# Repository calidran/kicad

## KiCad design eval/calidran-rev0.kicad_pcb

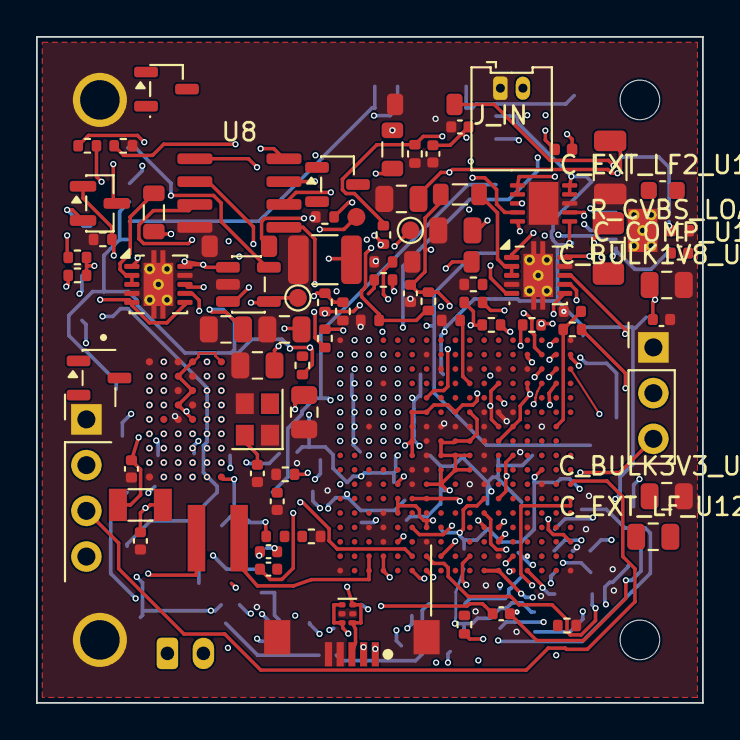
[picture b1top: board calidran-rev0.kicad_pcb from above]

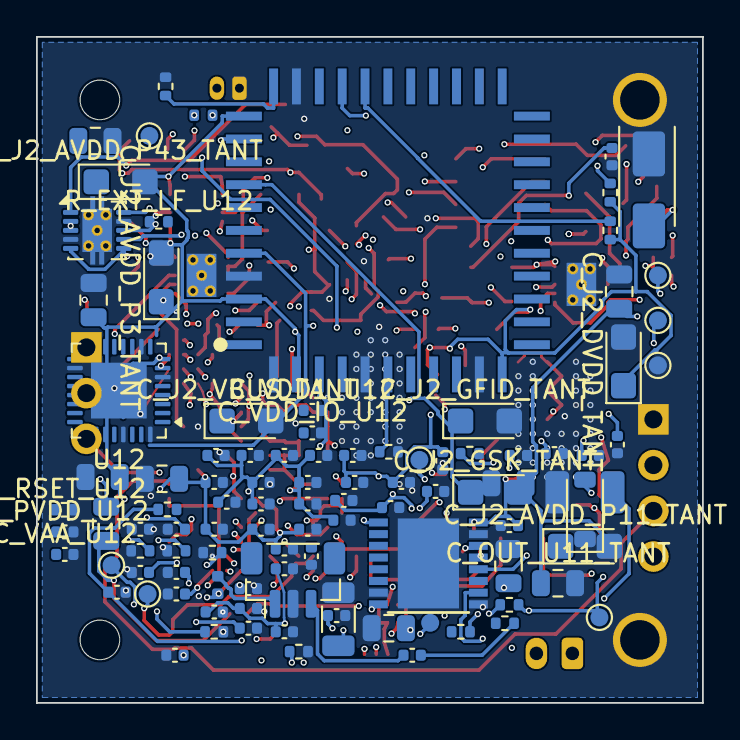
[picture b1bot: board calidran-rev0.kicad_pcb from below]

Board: 10 copper layers, 37.0 x 37.0 mm, 189 parts (101 on the bottom side), 140 nets.

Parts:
C1: 10uF_10V_X7R_0805; C_0805_2012Metric
C2, C5: 10uF_6V3_X5R_0805; C_0805_2012Metric
C3, C6: 4.7uF_6V3_X5R_0402; C_0402_1005Metric
C4: 10uF_25V_X5R; C_0805_2012Metric
C7: 10uF_25V_X7R_1206; C_1206_3216Metric
C8: 47uF_10V_X5R_1210; C_1210_3225Metric
C9, C14: 10uF_10V_X5R_0805; C_0805_2012Metric
C10, C11, C13: 100nF; C_0402_1005Metric
CFLY: 100nF_X5R_0402; C_0402_1005Metric
CVCP: 100nF; C_0402_1005Metric
CX1, CX2: 18pF_C0G_0402; C_0402_1005Metric
CX3, CX4: 6pF_C0G_0402_DNP; C_0402_1005Metric
C_ADC_VREF: 100nF; C_0402_1005Metric
C_ADJ_U11: 10nF_C0G; C_0402_1005Metric
C_ANA1: 2.2uF_0402; C_0402_1005Metric
C_BULK1V8_U12, C_BULK3V3_U12: 10uF_10V_X7R_0805; C_0805_2012Metric
C_COMP_U12: 2.2nF; C_0402_1005Metric
C_CVBS_AC: 100nF; C_0402_1005Metric
C_EXT_LF2_U12: 150nF; C_0603_1608Metric
C_EXT_LF_U12: 12nF; C_0805_2012Metric
C_FID_RSVR: 10uF; C_0402_1005Metric
C_IN_U11_FILM: 100nF; C_0805_2012Metric
C_IN_U11_TANT: 10uF_Tant; CP_EIA-3528-21_Kemet-B
C_J2_AVDD_P3_FILM, C_J2_AVDD_P11_FILM, C_J2_AVDD_P43_FILM, C_J2_DVDD_FILM, C_J2_GFID_FILM, C_J2_GSK_FILM, C_J2_VBUS_FILM: 100nF; C_0805_2012Metric
C_J2_AVDD_P3_TANT, C_J2_AVDD_P11_TANT, C_J2_AVDD_P43_TANT, C_J2_DVDD_TANT, C_J2_GFID_TANT, C_J2_GSK_TANT, C_J2_VBUS_TANT: 22uF_Tant; CP_EIA-3216-18_Kemet-A
C_J2_VRIN_FILM: 4.7uF; C_1206_3216Metric
C_LPSR_A: 100nF_0402; C_0402_1005Metric
C_LPSR_D: 100nF_0402; C_0402_1005Metric
C_MIPI1P0: 1uF_0402; C_0402_1005Metric
C_OUT_U11_FILM: 100nF; C_0805_2012Metric
C_OUT_U11_TANT: 10uF_16V_X7R; C_0805_2012Metric
C_PSWITCH: 100nF; C_0402_1005Metric
C_PVDD_U12: 100nF; C_0402_1005Metric
C_SNVS_A: 100nF_0402; C_0402_1005Metric
C_SNVS_D: 100nF_0402; C_0402_1005Metric
C_U6_1, C_U6_2, C_U6_3, C_U6_4, C_U6_5, C_U6_6, C_U6_15, C_U6_16, C_U6_17, C_U6_18, C_U6_19, C_U6_20, C_U6_21, C_U6_22, C_U6_23, C_U6_24, C_U6_25, C_U6_26, C_U7_1, C_U7_2, C_U7_3, C_U7_4: 100nF_X5R_0402; C_0402_1005Metric
C_U6_7, C_U6_8, C_U6_9, C_U6_10, C_U6_27, C_U6_28: 10uF_6V3_X5R_0402; C_0402_1005Metric
C_U6_11, C_U6_12, C_U6_13, C_U6_14: 10nF_X5R_0402; C_0402_1005Metric
C_VAA_U12: 100nF; C_0402_1005Metric
C_VDD1_U12: 100nF; C_0402_1005Metric
C_VDDA1P0: 2.2uF_0402; C_0402_1005Metric
C_VDD_IO_U12: 100nF; C_0402_1005Metric
C_VSYS_MON: 100nF; C_0402_1005Metric
D1: SMAJ18CA; D_SMA
D_FID: BAT54T3G; SOT-23-3
F1: MF-MSMF110/16X; Fuse_1206_3216Metric
FB1: FerriteBead_600R@100MHz; L_0402_1005Metric
F_VID: FSMD010-0402RZ; Fuse_0402_1005Metric
J2: PLU-044-H901-99; Conn_01x44_J_LEAD
JP1_BOOT: BOOT_MODE_JUMPER_DNP; PinHeader_1x03_P2.54mm_Vertical
J_3V3_SHUNT: 0R_DNP; R_0402_1005Metric
J_IN: Molex_PicoBlade_53048-0210_1x02_P1.25mm_Horizontal
J_SHUTTER: JST_PH_B2B-PH-K_1x02_P2.00mm_Vertical
J_UART: UART_Header_2.54mm; PinHeader_1x04_P2.54mm_Vertical
J_USB: USB_Micro-AB_Hirose_ZX62-AB-5PA
J_VIDEO: JST-SH_3pin_Video; JST_SH_BM03B-SRSS-TB_1x03-1MP_P1.00mm_Vertical
L1, L2, L3: 1uH_3A_Wurth_744066100; L_0805_2012Metric
L_DCDC: 4.7uH WE-MAPI; L_Wuerth_MAPI-4030
MK1, MK3: MountingHole_2.2mm_M2_Pad_R30
MK2, MK4: MountingHole_2.2mm_M2
Q1: SI2319DS-T1-GE3; SOT-23
Q_FID_N: 2N7002; SOT-23-3
Q_FID_P: Si2301CDS; SOT-23-3
R1: 49.9k; R_0402_1005Metric
R2: 200k; R_0402_1005Metric
R3: 124k; R_0402_1005Metric
R4, R6: 100k; R_0402_1005Metric
R5: 316k; R_0402_1005Metric
R_ADC_VREF: 10R; R_0402_1005Metric
R_BOOT_MODE0: 100k; R_0402_1005Metric
R_BOOT_MODE1: 4.7k; R_0402_1005Metric
R_BT_CFG0, R_BT_CFG1, R_BT_CFG4: 100k; R_0402_1005Metric
R_CVBS_LOAD: 75; R_0402_1005Metric
R_CVBS_SER: 75; R_0402_1005Metric
R_ENC_RESET_PU: 10k; R_0402_1005Metric
R_EN_U11: 100k; R_0402_1005Metric
R_EXT_LF_U12: 169; R_0402_1005Metric
R_FID: 10k; R_0402_1005Metric
R_G1: 1M; R_0402_1005Metric
R_HOLD: 10k; R_0402_1005Metric
R_ILIM_U11: DNP; R_0402_1005Metric
R_IPROPI: 10k; R_0402_1005Metric
R_J2_I2CAD, R_J2_SEQ_TRIG: 10k; R_0402_1005Metric
R_J2_SCL, R_J2_SDA: 4.7k; R_0402_1005Metric
R_JTAG_MOD: 4k7; R_0402_1005Metric
R_JTAG_TRST: 4k7; R_0402_1005Metric
R_NFAULT: 100k; R_0402_1005Metric
R_NSLEEP: 100k; R_0402_1005Metric
R_ONOFF: 100k; R_0402_1005Metric
R_PG1V0, R_PG1V8, R_PG3V3: 100k; R_0402_1005Metric
R_PG_U11: 100k; R_0402_1005Metric
R_PSWITCH: 100k; R_0402_1005Metric
R_RSET_U12: 510; R_0402_1005Metric
R_SET_U11: 37.4k; R_0402_1005Metric
R_TEST_MODE: 4k7; R_0402_1005Metric
R_VSYS_H: 100k; R_0402_1005Metric
R_VSYS_L: 22k1; R_0402_1005Metric
R_WAKEUP: 100k; R_0402_1005Metric
R_WP: 10k; R_0402_1005Metric
R_nRESET: 100k; R_0402_1005Metric
TP_3V3: TestPoint_Pad_D1.0mm
TP_BM0: TP_BM0; TestPoint_Pad_D1.0mm
TP_BM1: TP_BM1; TestPoint_Pad_D1.0mm
TP_GND: TestPoint_Pad_D1.0mm
TP_PG1V0: TP_PG1V0; TestPoint_Pad_D1.0mm
TP_PG1V8: TP_PG1V8; TestPoint_Pad_D1.0mm
TP_PG3V3: TP_PG3V3; TestPoint_Pad_D1.0mm
TP_PGOOD: TP_PGOOD; TestPoint_Pad_D1.0mm
TP_SWDCLK: TestPoint_Pad_D1.0mm
TP_SWDIO: TestPoint_Pad_D1.0mm
TP_SWO: TestPoint_Pad_D1.0mm
TP_nRST: TestPoint_Pad_D1.0mm
U1, U2, U3: TPS62130ARGTR; VSON-10-1EP_3x3mm_P0.5mm_EP1.65x2.4mm_ThermalVias
U4: TPS3840DL30DCKR; SOT-23-5
U6: MIMXRT1176DVMAA; MAPBGA-289_14x14mm_Layout17x17_P0.8mm
U7: AS4C32M16SB-7BIN
U8: W25Q128JV-IQ; SOIC-8_3.9x4.9mm_P1.27mm
U9: TPD4S012DRYR; Texas_USON-6_1x1.45mm_P0.5mm_SMD
U10: DRV8876PWPR; HTSSOP-16-1EP
U11: LT3045EDD#PBF; DFN-10-1EP_3x3mm_P0.5mm_EP1.65x2.38mm
U12: ADV7391BCPZ; QFN-32-1EP_5x5mm_P0.5mm_EP3.1x3.1mm
X1: 24MHz_NDK_NX2520SA-24.000MHZ; Crystal_SMD_2520-4Pin_2.5x2.0mm
X2: 32.768kHz_Epson_FC-135R_DNP; Crystal_SMD_3215-2Pin_3.2x1.5mm
Z1, Z2, Z3: BZT52C5V6-7-F; D_SOD-123
Z_G1: BZT52C5V6-7-F; D_SOD-123

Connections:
+1V8: C5.2, C6.2, C_BULK1V8_U12.1, C_EXT_LF2_U12.2, C_EXT_LF_U12.2, C_J2_DVDD_FILM.1, C_J2_DVDD_TANT.1, C_PVDD_U12.1, C_U6_5.2, C_U6_6.2, C_U6_23.2, C_U6_24.2, C_U6_25.2, C_U6_26.2, C_U6_27.2, C_U6_28.2, C_VDD1_U12.1, J2.34, L2.1, R3.1, R_J2_SCL.1, R_J2_SDA.1, R_PG1V8.1, U2.10, U6.D14, U6.F6, U6.F7, U6.F9, U6.G6, U6.G13, U6.H6, U6.H12, U6.J6, U6.K15, U6.M11, U12.5, U12.17, U12.28
+3V3: C8.2, C9.2, C11.2, C13.2, C14.2, C_BULK3V3_U12.1, C_COMP_U12.2, C_FID_RSVR.1, C_U7_1.2, C_U7_2.2, C_U7_3.2, C_U7_4.2, C_VAA_U12.1, C_VDD_IO_U12.1, FB1.2, F_VID.1, J_3V3_SHUNT.2, J_UART.2, L3.1, R5.1, R_BOOT_MODE1.1, R_ENC_RESET_PU.1, R_EN_U11.1, R_HOLD.2, R_JTAG_TRST.2, R_NFAULT.1, R_NSLEEP.1, R_PG3V3.1, R_PSWITCH.2, R_WP.2, TP_3V3.1, U3.10, U4.1, U4.3, U6.D12, U6.E7, U6.G12, U6.J13, U6.M5, U6.M12, U6.N5, U6.P7, U6.R12, U6.U11, U6.U12, U7.A4, U7.A6, U7.B3, U7.C4, U7.D3, U7.E4, U7.J6, U8.8, U10.5, U10.16, U12.1, U12.19
+12V_IN: C1.2, C4.2, C7.2, CVCP.2, D1.2, Q1.2, U1.5, U1.6, U2.5, U2.6, U3.5, U3.6, U10.11
/+1V0: C2.2, C3.2, C_MIPI1P0.2, C_U6_1.2, C_U6_2.2, C_U6_3.2, C_U6_4.2, C_U6_7.2, C_U6_8.2, C_U6_9.2, C_U6_10.2, C_U6_11.2, C_U6_12.2, C_U6_13.2, C_U6_14.2, C_U6_15.2, C_U6_16.2, C_U6_17.2, C_U6_18.2, C_U6_19.2, C_U6_20.2, C_U6_21.2, C_U6_22.2, L1.1, R1.1, R_PG1V0.1, U1.10, U6.F10, U6.H8, U6.H9, U6.H10, U6.J8, U6.J9, U6.J10, U6.K8, U6.K9, U6.K10, U6.L7, U6.L8
/+3V3_MEAS: J_3V3_SHUNT.1, R_ADC_VREF.2, R_ONOFF.2, R_nRESET.2
/+3V3_VID: F_VID.2, J_VIDEO.1
/ADC_VREFH: C_ADC_VREF.2, R_ADC_VREF.1, U6.G16
/BOOT_MODE0: JP1_BOOT.3, R_BOOT_MODE0.2, TP_BM0.1, U6.P6
/BOOT_MODE1: JP1_BOOT.2, R_BOOT_MODE1.2, TP_BM1.1, U6.T7
/CVBS_MID: C_CVBS_AC.1, R_CVBS_SER.2
/DCDC_ANA: C_ANA1.2, U6.M6, U6.M7, U6.M8
/DCDC_IN_Q: FB1.1, U6.L5
/DCDC_LN: L_DCDC.1, U6.T4, U6.U4
/DCDC_LP: L_DCDC.2, U6.T3, U6.U3
/ENC_CLK27: U6.E13, U12.13
/ENC_D0: U6.E10, U12.30
/ENC_D1: U6.C11, U12.31
/ENC_D2: R_BT_CFG0.2, U6.D10, U12.2
/ENC_D3: R_BT_CFG1.2, U6.E12, U12.3
/ENC_D4: U6.A15, U12.4
/ENC_D5: U6.C13, U12.7
/ENC_D6: R_BT_CFG4.2, U6.B14, U12.8
/ENC_D7: U6.A14, U12.9
/EN_1V0: U1.1, Z1.2
/EN_1V8: U2.1, Z2.2
/EN_3V3: U3.1, Z3.2
/EXT_LF_FZ: C_EXT_LF2_U12.1, R_EXT_LF_U12.2
/FB_1V0: R1.2, R2.2, U1.7
/FB_1V8: R3.2, R4.2, U2.7
/FB_3V3: R5.2, R6.2, U3.7
/JTAG_MOD: R_JTAG_MOD.2, U6.U6
/JTAG_TRSTB: R_JTAG_TRST.1, U6.R5
/ONOFF: R_ONOFF.1, U6.U10
/PG_1V0: R_PG1V0.2, TP_PG1V0.1, U1.8
/PG_1V8: R_PG1V8.2, TP_PG1V8.1, U2.8
/PG_3V3: R_PG3V3.2, TP_PG3V3.1, U3.8
/Q1_GATE: Q1.1, R_G1.2, Z_G1.2
/QSPI_CLK: U6.D15, U8.6
/QSPI_CS0_B: U6.B16, U8.1
/QSPI_D0: U6.C15, U8.5
/QSPI_D1: U6.B17, U8.2
/QSPI_D2: R_WP.1, U6.B15, U8.3
/QSPI_D3: R_HOLD.1, U6.A16, U8.7
/RTC_XTAL_IN: CX3.2, U6.T13, X2.1
/RTC_XTAL_OUT: CX4.2, U6.U13, X2.2
/SEMC_A0: U6.A3, U7.G2
/SEMC_A1: U6.A2, U7.G1
/SEMC_A2: U6.C2, U7.J3
/SEMC_A3: U6.C5, U7.H3
/SEMC_A4: U6.D5, U7.J5
/SEMC_A5: U6.B1, U7.H1
/SEMC_A6: U6.C1, U7.J4
/SEMC_A7: U6.D3, U7.J2
/SEMC_A8: U6.B3, U7.H2
/SEMC_A9: U6.B4, U7.H6
/SEMC_A10: U6.B2, U7.G3
/SEMC_A11: U6.C4, U7.H4
/SEMC_A12: U6.C3, U7.H5
/SEMC_BA0: U6.G2, U7.G4
/SEMC_BA1: U6.H2, U7.G5
/SEMC_CAS_B: U6.J4, U7.F4
/SEMC_CKE: U6.E5, U7.F3
/SEMC_CLK: U6.G5, U7.F2
/SEMC_CS0_B: U6.L1, U7.G6
/SEMC_D0: U6.F3, U7.B6
/SEMC_D1: U6.F2, U7.C5
/SEMC_D2: U6.G4, U7.C6
/SEMC_D3: U6.E4, U7.A5
/SEMC_D4: U6.H5, U7.D6
/SEMC_D5: U6.F4, U7.B5
/SEMC_D6: U6.H4, U7.D5
/SEMC_D7: U6.H3, U7.E6
/SEMC_D8: U6.E3, U7.B1
/SEMC_D9: U6.D2, U7.A2
/SEMC_D10: U6.D1, U7.B2
/SEMC_D11: U6.E2, U7.C2
/SEMC_D12: U6.E1, U7.C1
/SEMC_D13: U6.F1, U7.D2
/SEMC_D14: U6.G1, U7.D1
/SEMC_D15: U6.H1, U7.E1
/SEMC_DQM0: U6.F5, U7.E5
/SEMC_DQM1: U6.E6, U7.F1
/SEMC_RAS_B: U6.J5, U7.F5
/SEMC_WE_B: U6.J3, U7.F6
/SHUTTER_IN1: U6.R17, U10.1
/SHUTTER_IN2: U6.P16, U10.2
/SHUTTER_IPROPI: R_IPROPI.1, U6.L12, U10.6
/SHUTTER_NFAULT: R_NFAULT.2, U6.N14, U10.4
/SHUTTER_OUT1: J_SHUTTER.1, U10.8
/SHUTTER_OUT2: J_SHUTTER.2, U10.10
/SH_CPH: CFLY.1, U10.13
/SH_CPL: CFLY.2, U10.14
/SH_NSLEEP: R_NSLEEP.2, U10.3
/SH_VCP: CVCP.1, U10.12
/SWDCLK: TP_SWDCLK.1, U6.T6
/SWDIO: TP_SWDIO.1, U6.U7
/SWO: TP_SWO.1, U6.T5
/SW_1V0: L1.2, U1.2, U1.3
/SW_1V8: L2.2, U2.2, U2.3
/SW_3V3: L3.2, U3.2, U3.3
/SYS_RST_B: R_nRESET.1, TP_PGOOD.1, TP_nRST.1, U4.4, U6.T10
/TEST_MODE: R_TEST_MODE.2, U6.T11
/U4_CT: C10.2, U4.5
/U12_COMP: C_COMP_U12.1, U12.23
/U12_EXT_LF: C_EXT_LF_U12.1, R_EXT_LF_U12.1, U12.16
/U12_RSET: R_RSET_U12.1, U12.24
/UART_RX: J_UART.4, U6.M17
/UART_TX: J_UART.3, U6.L17
/USB_DM: J_USB.2, U6.C16, U9.4, U9.6
/USB_DP: J_USB.3, U6.C17, U9.1, U9.3
/USB_VBUS: J_USB.1, U6.D16
/VDDA_1P0: C_VDDA1P0.2, U6.N11
/VDD_LPSR_ANA: C_LPSR_A.2, U6.P12
/VDD_LPSR_DIG: C_LPSR_D.2, U6.P11
/VDD_SNVS_ANA: C_SNVS_A.2, U6.U14
/VDD_SNVS_DIG: C_SNVS_D.2, U6.T14
/VIN_FUSED: F1.2, Q1.3
/VIN_RAW: F1.1, J_IN.2
/WAKEUP: R_WAKEUP.2, U6.T8
/XTAL24_IN: CX1.2, U6.U16, X1.4
/XTAL24_OUT: CX2.2, U6.T16, X1.2
AVDD: C_ADJ_U11.2, C_J2_AVDD_P3_FILM.1, C_J2_AVDD_P3_TANT.1, C_J2_AVDD_P11_FILM.1, C_J2_AVDD_P11_TANT.1, C_J2_AVDD_P43_FILM.1, C_J2_AVDD_P43_TANT.1, C_J2_GSK_FILM.1, C_J2_GSK_TANT.1, C_OUT_U11_FILM.1, C_OUT_U11_TANT.1, J2.3, J2.11, J2.43, R_PG_U11.2, U11.6, U11.9, U11.10
CVBS_OUT: C_CVBS_AC.2, J_VIDEO.3
CVBS_RAW: R_CVBS_LOAD.1, R_CVBS_SER.1, U12.22
ENC_RESET: R_ENC_RESET_PU.2, U6.R15, U12.14
GND: C1.1, C2.1, C3.1, C4.1, C5.1, C6.1, C7.1, C8.1, C9.1, C10.1, C11.1, C13.1, C14.1, CX1.1, CX2.1, CX3.1, CX4.1, C_ADC_VREF.1, C_ANA1.1, C_BULK1V8_U12.2, C_BULK3V3_U12.2, C_FID_RSVR.2, C_IN_U11_FILM.2, C_IN_U11_TANT.2, C_J2_AVDD_P3_FILM.2, C_J2_AVDD_P3_TANT.2, C_J2_AVDD_P11_FILM.2, C_J2_AVDD_P11_TANT.2, C_J2_AVDD_P43_FILM.2, C_J2_AVDD_P43_TANT.2, C_J2_DVDD_FILM.2, C_J2_DVDD_TANT.2, C_J2_GFID_FILM.2, C_J2_GFID_TANT.2, C_J2_VBUS_FILM.2, C_J2_VBUS_TANT.2, C_J2_VRIN_FILM.2, C_LPSR_A.1, C_LPSR_D.1, C_MIPI1P0.1, C_OUT_U11_FILM.2, C_OUT_U11_TANT.2, C_PSWITCH.1, C_PSWITCH.2, C_PVDD_U12.2, C_SNVS_A.1, C_SNVS_D.1, C_U6_1.1, C_U6_2.1, C_U6_3.1, C_U6_4.1, C_U6_5.1, C_U6_6.1, C_U6_7.1, C_U6_8.1, C_U6_9.1, C_U6_10.1, C_U6_11.1, C_U6_12.1, C_U6_13.1, C_U6_14.1, C_U6_15.1, C_U6_16.1, C_U6_17.1, C_U6_18.1, C_U6_19.1, C_U6_20.1, C_U6_21.1, C_U6_22.1, C_U6_23.1, C_U6_24.1, C_U6_25.1, C_U6_26.1, C_U6_27.1, C_U6_28.1, C_U7_1.1, C_U7_2.1, C_U7_3.1, C_U7_4.1, C_VAA_U12.2, C_VDD1_U12.2, C_VDDA1P0.1, C_VDD_IO_U12.2, C_VSYS_MON.2, D1.1, J2.4, J2.13, J2.35, J2.40, J2.44, JP1_BOOT.1, J_IN.1, J_UART.1, J_USB.4, J_USB.5, J_USB.6, J_VIDEO.2, MK1.1, MK3.1, R2.1, R4.1, R6.1, R_BOOT_MODE0.1, R_BT_CFG0.1, R_BT_CFG1.1, R_BT_CFG4.1, R_CVBS_LOAD.2, R_FID.2, R_G1.1, R_ILIM_U11.2, R_IPROPI.2, R_J2_I2CAD.2, R_J2_SEQ_TRIG.2, R_JTAG_MOD.1, R_PSWITCH.1, R_RSET_U12.2, R_SET_U11.1, R_TEST_MODE.1, R_VSYS_L.2, R_WAKEUP.1, TP_GND.1, U1.4, U1.9, U1.11, U2.4, U2.9, U2.11, U3.4, U3.9, U3.11, U4.2, U6.A1, U6.A17, U6.B7, U6.C8, U6.C10, U6.C12, U6.C14, U6.D4, U6.F11, U6.F12, U6.F13, U6.G3, U6.G7, U6.G8, U6.G9, U6.G10, U6.G11, U6.G15, U6.H7, U6.H11, U6.J7, U6.J11, U6.K6, U6.K7, U6.K11, U6.L3, U6.L6, U6.L10, U6.L11, U6.L15, U6.N4, U6.P3, U6.P4, U6.P14, U6.R4, U6.R7, U6.T12, U6.U1, U6.U17, U7.A1, U7.A3, U7.B4, U7.C3, U7.D4, U7.E3, U7.J1, U8.4, U9.2, U9.5, U10.7, U10.9, U10.15, U10.17, U11.8, U11.11, U12.6, U12.10, U12.15, U12.18, U12.29, U12.32, U12.33, X1.1, X1.3, Z1.1, Z2.1, Z3.1, Z_G1.1
J2_GFID: C_J2_GFID_FILM.1, C_J2_GFID_TANT.1, J2.10
J2_GSK: C_J2_GSK_FILM.2, C_J2_GSK_TANT.2, J2.8
J2_I2CAD: J2.12, R_J2_I2CAD.1
J2_SCL: J2.16, R_J2_SCL.2, U12.12
J2_SDA: J2.15, R_J2_SDA.2, U12.11
J2_SEQ_TRIG: J2.39, R_J2_SEQ_TRIG.1
J2_VBUS: C_J2_VBUS_FILM.1, C_J2_VBUS_TANT.1, J2.5
J2_VRIN: C_J2_VRIN_FILM.1, J2.42
U11_EN: R_EN_U11.2, U11.3
U11_ILIM: R_ILIM_U11.1, U11.5
U11_PG: R_PG_U11.1, U11.4
U11_SET: C_ADJ_U11.1, R_SET_U11.2, U11.7
VIN_FUSED: C_IN_U11_FILM.1, C_IN_U11_TANT.1, U11.1, U11.2
VSYS_MON_DIV: C_VSYS_MON.1, R_VSYS_H.2, R_VSYS_L.1
